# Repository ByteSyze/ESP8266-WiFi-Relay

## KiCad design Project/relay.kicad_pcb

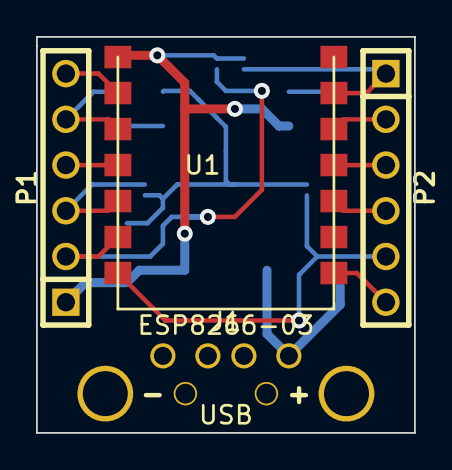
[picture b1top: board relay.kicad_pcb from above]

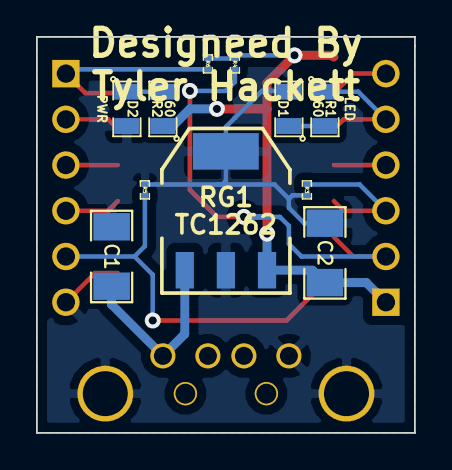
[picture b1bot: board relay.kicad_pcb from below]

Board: 2 copper layers, 21.0 x 22.0 mm, 15 parts (11 on the bottom side), 15 nets.

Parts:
C1, C2: 10uF; SM1206
D1: LED; SM0805
D2: PWR; SM0805
J1: USB; USB-A
P1, P2: CONN_6; PIN_ARRAY-6X1
R1, R2: 60; SM0805
R3, R4, R5, R6: J; SM0201_r
RG1: TC1262; SOT223
U1: ESP8266-03

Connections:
GND: C1.2, C2.2, D1.2, D2.2, J1.4, J1.5, J1.6, P2.6, R3.2, R5.2, RG1.2, RG1.4, U1.8
unnamed: D1.1, R1.2
unnamed: P1.6, U1.2
unnamed: P1.3, R3.1, U1.5
unnamed: P1.4, U1.4
unnamed: P1.5, R1.1, U1.3
unnamed: P2.3, U1.11
unnamed: P2.4, U1.10
unnamed: P2.2, U1.12
unnamed: D2.1, R2.2
unnamed: P2.5, R5.1, U1.7
unnamed: P1.2, R4.2, U1.6
unnamed: P2.1, R6.2, U1.13
unnamed: C1.1, J1.1, RG1.1
VCC: C2.1, P1.1, R2.1, R4.1, R6.1, RG1.3, U1.1

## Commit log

2014-12-01 :circus_tent: Added .gitattributes & .gitignore files
2014-12-01 A little organizing
2015-01-20 Lots of enhancements to PCB
    Added pins for VCC and GND, downsized PCB footprint, Added solder
    jumpers to permanently pull up/down various pins.
